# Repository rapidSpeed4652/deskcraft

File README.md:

# DeskCraft
An AI-powered desk robot that responds to voice commands and can use inbuilt camera to use pictures as context for answers.
The AI model is run on a PC which communicates directly with the robot.

(If it looks very green, try disabling the Edge.Cuts layer from the layers tab)

## Features
- Responds to voice commands
- Uses camera as context
- Utilises local AI model
- No battery, no charging (so no worries :D)
- Shows expressions and gestures

## PCB

## CAD
### Head of robot

### Body of robot

### Complete robot

(i swear it will look better irl :P)

## Onshape url
https://cad.onshape.com/documents/b63407ed3120d82d91f122be/w/f6937e50d8bbef57107a5206/e/a72c19b49a035d7c3cf8bcb7

## BOM
- 1x Seeed esp32 s3 sense
- 1x 1.54" 7-pin SPI OLED Display
- 1x Adafruit MAX98357A Breakout Board
- 1x Mini Speaker
- 2x 3D printed case (head+body)
- 7x Jumper cables (Male to Female)
- 1x 1x7 Female Pin Header (2.54mm)

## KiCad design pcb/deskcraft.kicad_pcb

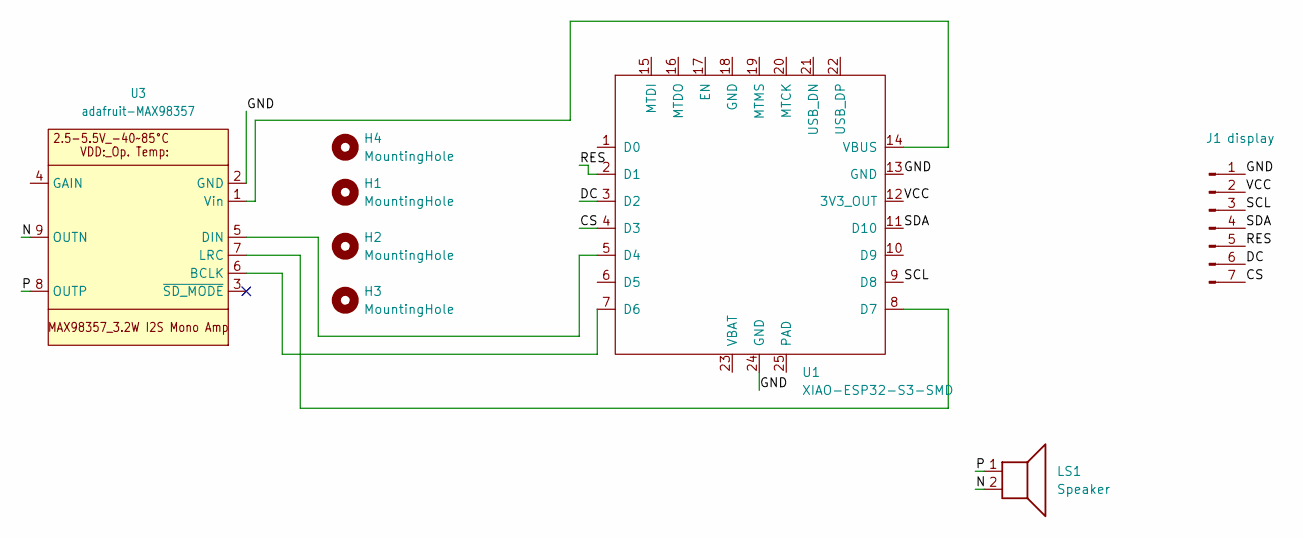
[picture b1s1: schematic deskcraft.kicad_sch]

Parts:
H1, H2, H3, H4: MountingHole; MountingHole_2.2mm_M2
J1: display; PinHeader_1x07_P1.00mm_Vertical
LS1: Speaker; JST_PH_B2B-PH-K_1x02_P2.00mm_Vertical
U1: XIAO-ESP32-S3-SMD
U3: adafruit-MAX98357

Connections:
/CS: J1.7, U1.4 (D3)
/DC: J1.6, U1.3 (D2)
/GND: J1.1, U1.13 (GND), U1.24 (GND), U3.2 (GND)
/N: LS1.2, U3.9 (OUTN)
/P: LS1.1, U3.8 (OUTP)
/RES: J1.5, U1.2 (D1)
/SCL: J1.3, U1.9 (D8)
/SDA: J1.4, U1.11 (D10)
/VCC: J1.2, U1.12 (3V3_OUT)
unnamed: U1.5 (D4), U3.5 (DIN)
unnamed: U1.7 (D6), U3.6 (BCLK)
unnamed: U1.8 (D7), U3.7 (LRC)
unnamed: U1.14 (VBUS), U3.1 (Vin)

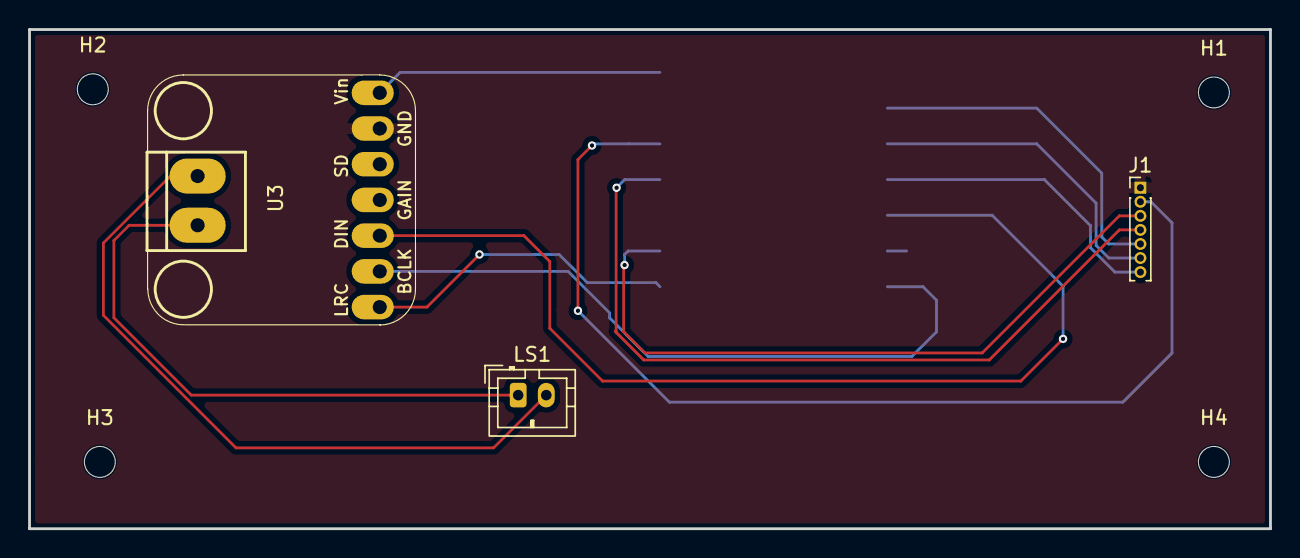
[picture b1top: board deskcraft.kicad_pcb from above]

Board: 2 copper layers, 88.2 x 35.5 mm, 8 parts (1 on the bottom side), 13 nets.

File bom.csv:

"Reference","Qty","Value","DNP","Exclude from BOM","Exclude from Board","Footprint","Datasheet"
"J1","1","display","","","","Connector_PinHeader_1.00mm:PinHeader_1x07_P1.00mm_Vertical",""
"LS1","1","Speaker","","","","Connector_JST:JST_PH_B2B-PH-K_1x02_P2.00mm_Vertical",""
"U1","1","XIAO-ESP32-S3-SMD","","","","New_XIAO_Series_Footprints:XIAO-ESP32-S3-SMD",""
"U3","1","adafruit-MAX98357","","","","footprints:adafruit-MAX98357","https://learn.adafruit.com/adafruit-max98357-i2s-class-d-mon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"
